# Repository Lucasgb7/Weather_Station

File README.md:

## LPWAN Weather Station

A LPWAN Weather Station using LoRaWAN technology. The monitored environment variables are: temperature, humidity, atmospheric pressure, UV intensity, wind speed and wind direction.

Check out the full project building on: [Instructables](https://www.instructables.com/LoRaWAN-Automatic-Weather-Station/).

## Installation

Installation steps are easy to be followed you can build your own steps if you want, but I'll show what were my steps.

### Environment Setup

1. Install [Visual Studio Code](https://code.visualstudio.com/).
2. Install [PlatformIO](https://docs.platformio.org/en/latest/integration/ide/vscode.html#installation) extension  on VSCode.
3. Create a PlatformIO project on VSCode selecting the *ESP32 DEVKIT V1* board.
4. Clone this repository ;)

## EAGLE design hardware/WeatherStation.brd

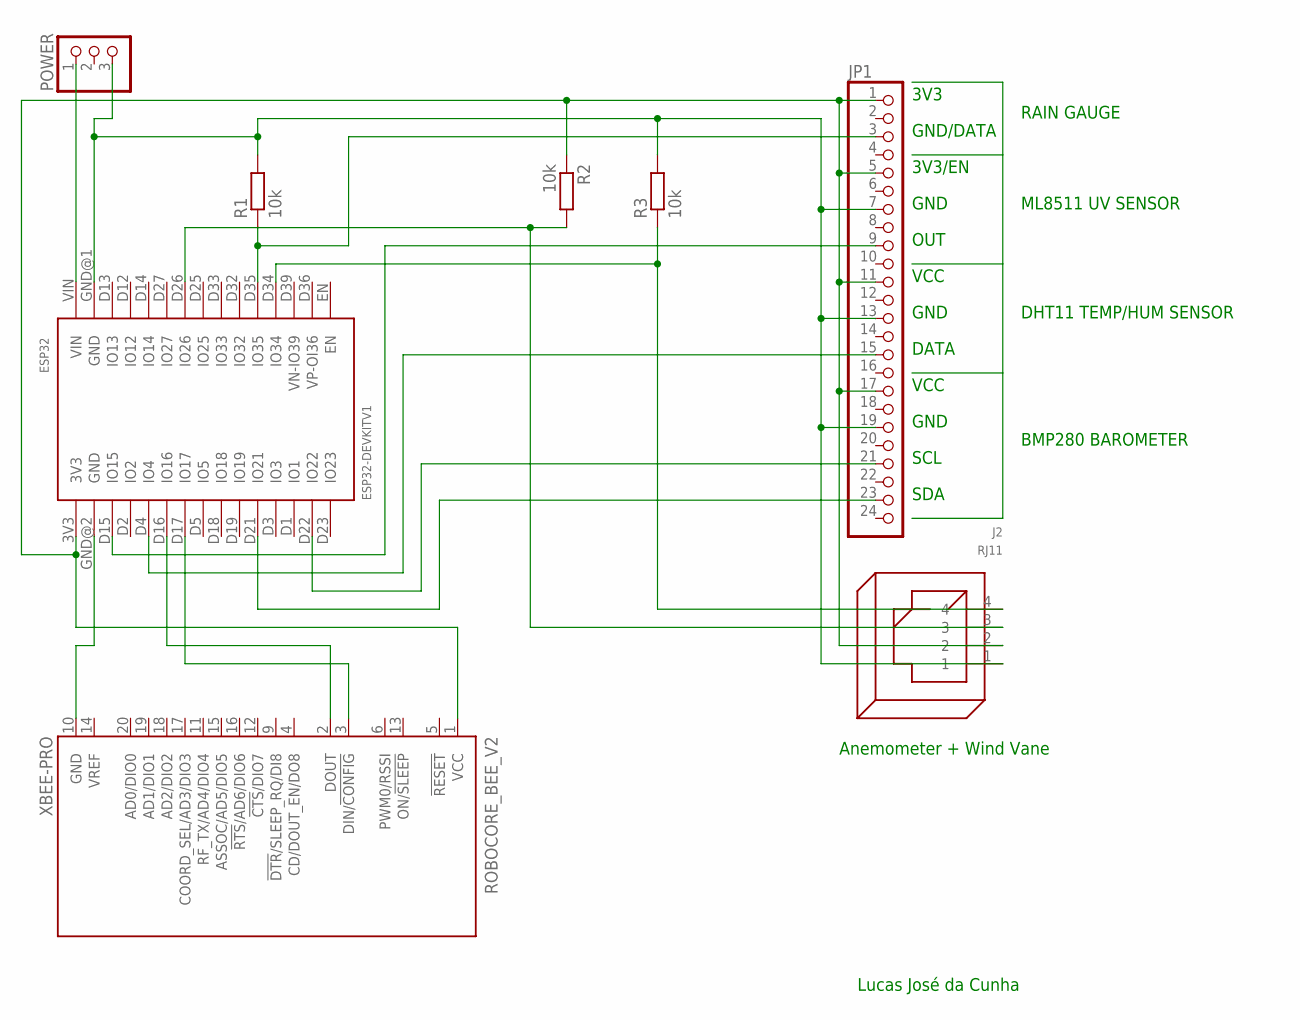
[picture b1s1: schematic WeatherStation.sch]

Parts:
ESP32: ESP32DEVKITV1; ESP32-DEVKITV1
J2: RJ11
JP1: PINHD-1X24; 1X24
POWER: PINHD-1X3; 1X03
R1, R2, R3: 10k; 0204/7
ROBOCORE_BEE_V2: XBEE-PRO

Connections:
unnamed: ESP32.3V3, J2.2, JP1.1, JP1.5, JP1.11, JP1.17, R2.1, ROBOCORE_BEE_V2.1 (VCC)
unnamed: ESP32.D26 (IO26), J2.3, R2.2
unnamed: ESP32.D35 (IO35), JP1.3, R1.1
unnamed: ESP32.D15 (IO15), JP1.9
unnamed: ESP32.D16 (IO16), ROBOCORE_BEE_V2.2 (DOUT)
unnamed: ESP32.GND@2 (GND), ROBOCORE_BEE_V2.10 (GND)
unnamed: ESP32.D4 (IO4), JP1.15
unnamed: ESP32.VIN, POWER.1
unnamed: ESP32.D22 (IO22), JP1.21
unnamed: ESP32.D21 (IO21), JP1.23
unnamed: ESP32.D17 (IO17), ROBOCORE_BEE_V2.3 (DIN/!CONFIG)
unnamed: ESP32.GND@1 (GND), J2.1, JP1.7, JP1.13, JP1.19, POWER.3, R1.2, R3.2
unnamed: ESP32.D34 (IO34), J2.4, R3.1

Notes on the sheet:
Anemometer + Wind Vane
3V3
GND/DATA
3V3/EN
GND
VCC
OUT
DATA
SCL
SDA
RAIN GAUGE
ML8511 UV SENSOR
DHT11 TEMP/HUM SENSOR
BMP280 BAROMETER
Lucas José da Cunha

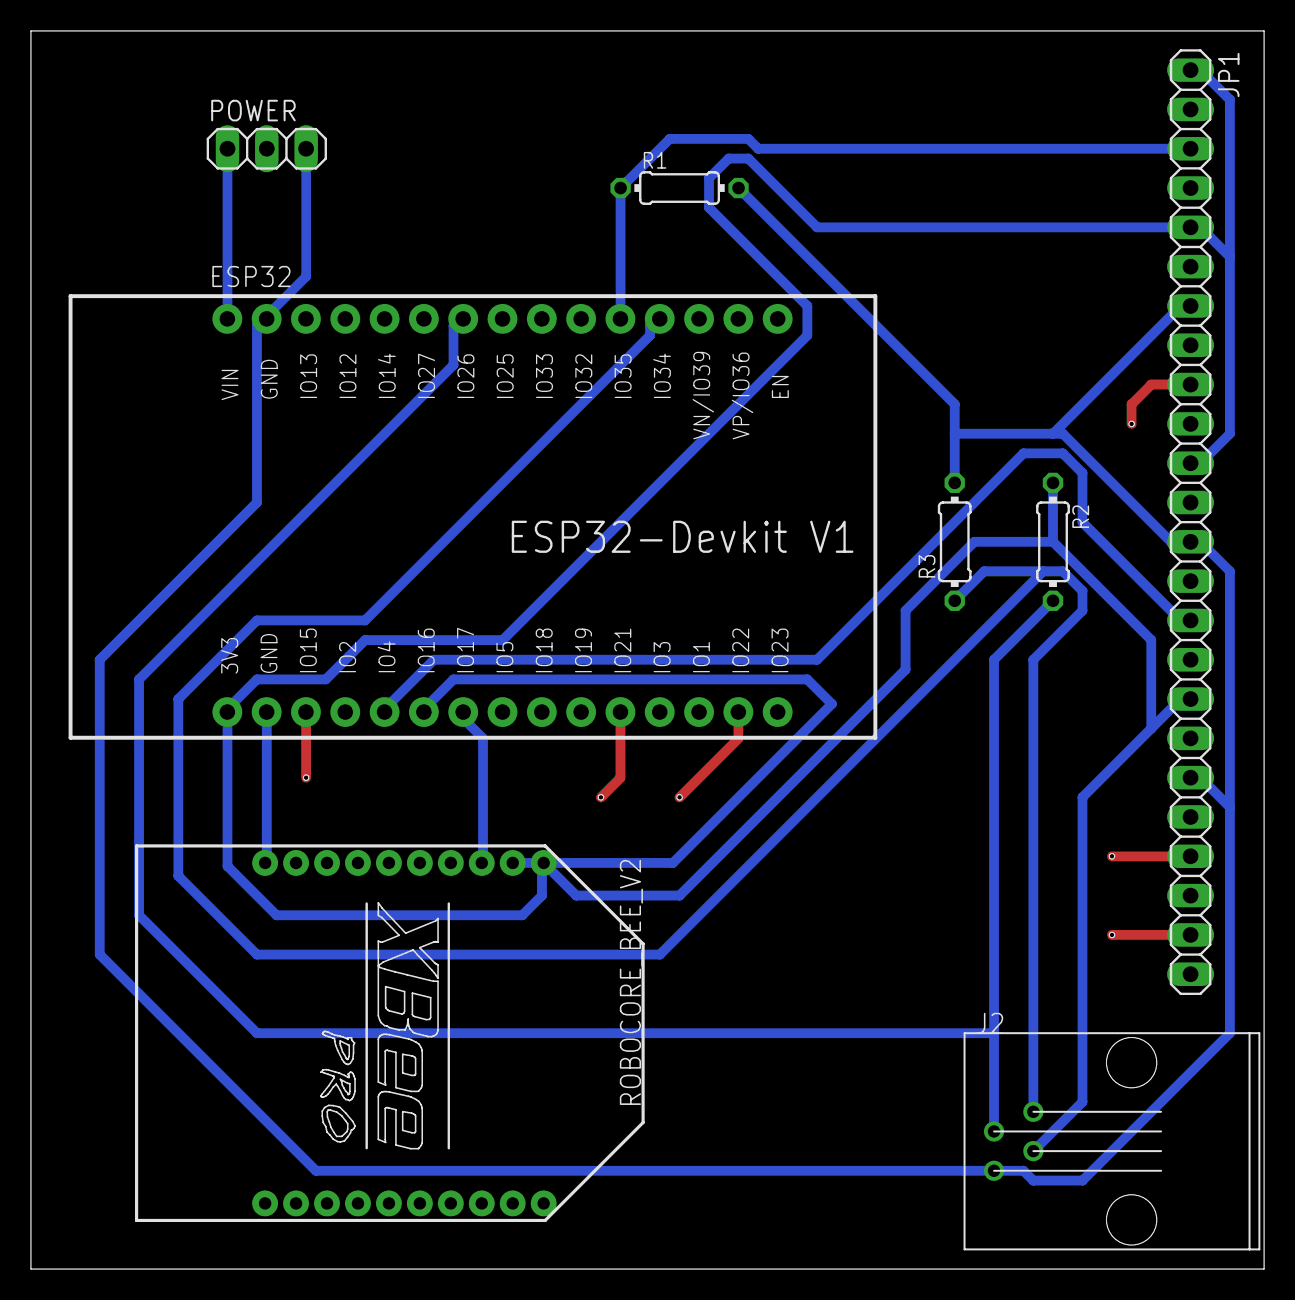
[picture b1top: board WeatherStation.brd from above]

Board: 2 copper layers, 79.7 x 80.0 mm, 8 parts (0 on the bottom side), 13 nets.

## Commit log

2021-07-07 iniciando repositorio no PlatformIO
2021-07-07 teste temperatura/umidade
2021-07-07 teste com sensor de pressao atmosferica
2021-07-08 configuracoes de execucao
2021-07-08 sensor de radiacao solar
2021-08-17 deteccao de endereco de disp. i2C
2021-08-17 prototipo no fritzing
2021-08-18 add biblioteca ADSWeather
2021-08-18 monitorando todas as variaveis (melhorar valores)
2021-08-21 TENTANDO DESMENBRAR O CATA-VENTO
2021-08-26 lorawan module library
2021-08-26 wind vane still compromised, starting with lorawan
2021-08-26 library robocore error [reorder]
2021-08-26 hidding lorawan keys
2021-08-26 JSON format data
2021-08-26 chaning names, comments, libraries, and adding LoRaWAN settings
2021-08-27 first readme update
2021-08-27 link mistakes
2021-08-28 print data function, wind direction values, reading times
2021-08-28 removing adweather library
2021-08-29 ready to check lorawan connection
2021-09-03 alterando nome do STATUS_LED
2021-09-03 protoboard fixed
2021-09-03 squematic and board
2021-09-04 fixing schematic v1.1
2021-09-17 ignore att on extension.json
2021-09-17 timestamp in serial monitor
2021-09-17 removing arduino's code
2021-09-17 changing keys and setting ABP mode (test)
2021-09-21 decreasing payload length, validate abp method, testing sensors in pcb
2021-09-23 rain gauge delay
2021-09-23 changing rain gauge and wind sensor connection
2021-09-27 a better prototype
2021-10-05 decreasing comsuptiom with deep sleep
2021-10-05 testing connectiong with painel solar (not working)
2021-10-08 adding features on RoboCore library
2021-10-08 forgot a file
2021-10-08 setting region when starts
2021-10-08 changing window rx delays in the library
2021-10-08 setting the correct values in window rx
2021-10-09 adafruit busio library
2021-10-13 deacreasing cpu frequency
2021-10-13 comments, removing deep sleep, 15min sending data
2021-10-14 modem sleep
2021-10-16 change frequency for dht11 works
2021-10-21 updating schematic, better board, and portuguese fzz
2021-10-27 second check on temperature and humidity
2021-10-27 trying to set RX1DL and RX2DL
2021-10-27 changing tick couting to millis()
2021-10-28 rain time = 10min; rain time reading = 1h;
2021-10-29 removing RTC variable
2021-11-01 reading rain first
2021-11-09 changes at reading sequence
2021-11-09 reading ProIoT json data
2021-11-11 data validation
2021-11-25 updating instructable link
2021-11-30 november data
